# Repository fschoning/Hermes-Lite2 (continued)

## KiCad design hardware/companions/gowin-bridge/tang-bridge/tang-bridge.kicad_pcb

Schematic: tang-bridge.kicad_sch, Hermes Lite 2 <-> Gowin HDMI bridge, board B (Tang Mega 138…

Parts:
C1: 22pF; C_0402_1005Metric; LCSC C1555; not fitted
C2, C3, C4, C5, C6, C7, C8, C9, C10: 100nF; C_0402_1005Metric; LCSC C1525; not fitted
C11, C12, C13, C14, C15, C16, C17, C19, C21, C23: 100nF; C_0402_1005Metric; LCSC C1525
C18, C20, C22: 10uF; C_0805_2012Metric; LCSC C15850
D1, D2, D3, D4, D5, D6, D7, D8, D9: TPD4E05U06; USON-10_2.5x1.0mm_P0.5mm; LCSC C138714
H1, H2: M3; MountingHole_3.2mm_M3_Pad
J1: J14 2x20 socket; PinSocket_2x20_P2.54mm_Vertical; not fitted
J2: IN (HDMI); HDMI_A_Amphenol_10029449-x01xLF_Horizontal; LCSC C427307
J3: AUX (HDMI); HDMI_A_Amphenol_10029449-x01xLF_Horizontal; LCSC C427307
J4: OUT (HDMI); HDMI_A_Amphenol_10029449-x01xLF_Horizontal; LCSC C427307
J5: RX MODE; PinHeader_1x03_P2.54mm_Vertical; not fitted
J6: GND AUX; PinHeader_1x02_P2.54mm_Vertical; not fitted
J7: ROLE; PinHeader_1x03_P2.54mm_Vertical; not fitted
R1, R2, R3, R4, R17, R19, R21, R23, R25, R27, R29, R31: 22R; R_0402_1005Metric; LCSC C25092
R5, R6, R7, R8, R9, R10, R11, R12, R13, R14, R15, R16, R42: 0R; R_0402_1005Metric; LCSC C17168; not fitted
R18, R20, R22, R24, R26, R28, R30, R32, R34, R35, R41: 10k; R_0402_1005Metric; LCSC C25744
R33, R36, R37, R46, R47, R51, R52, R56, R57, R61, R62: 0R; R_0402_1005Metric; LCSC C17168
R38, R48, R53, R58, R63, R68, R69: 100R; R_0402_1005Metric; LCSC C25076
R39, R40: 100k; R_0402_1005Metric; LCSC C25741
R43, R44, R45: 0R; R_0805_2012Metric; LCSC C17477
R49, R50, R54, R55, R59, R60, R64, R65, R67: 4k7; R_0402_1005Metric; LCSC C25900; not fitted
R66: 10k; R_0402_1005Metric; LCSC C25744; not fitted
R70, R71: 100R; R_0402_1005Metric; LCSC C25076; not fitted
TP1: TP_LINK_CLK; TestPoint_Pad_D1.5mm
TP2: TP_LINK_D0; TestPoint_Pad_D1.5mm
TP3: TP_LINK_D1; TestPoint_Pad_D1.5mm
TP4: TP_LINK_D2; TestPoint_Pad_D1.5mm
TP5: TP_LINK_SLOW_IN; TestPoint_Pad_D1.5mm
TP6: TP_LINK_AUX_G1_CLK; TestPoint_Pad_D1.5mm
TP7: TP_LINK_AUX_G1_DAT; TestPoint_Pad_D1.5mm
TP8: TP_LINK_AUX_G2_CLK; TestPoint_Pad_D1.5mm
TP9: TP_LINK_AUX_G2_DAT; TestPoint_Pad_D1.5mm
TP10: TP_LINK_PRESENT; TestPoint_Pad_D1.5mm
TP11: TP_LINK_ROLE; TestPoint_Pad_D1.5mm
TP12: TP_LINK_REVCLK; TestPoint_Pad_D1.5mm
TP13: TP_LINK_R0; TestPoint_Pad_D1.5mm
TP14: TP_LINK_R1; TestPoint_Pad_D1.5mm
TP15: TP_LINK_R2; TestPoint_Pad_D1.5mm
TP16: TP_DRVI_REVCLK; TestPoint_Pad_D1.5mm
TP17: TP_ROLE; TestPoint_Pad_D1.5mm
TP18: TP_ROLE_N; TestPoint_Pad_D1.5mm
TP19: TP_RXO_AX_CLK; TestPoint_Pad_D1.5mm
TP20: TP_RXO_AX_D0; TestPoint_Pad_D1.5mm
TP21: TP_RXO_AX_D1; TestPoint_Pad_D1.5mm
TP22: TP_RXO_AX_D2; TestPoint_Pad_D1.5mm
TP23: TP_I_HPD; TestPoint_Pad_D1.5mm
TP24: TP_AX_HPD; TestPoint_Pad_D1.5mm
TP25: TP_O_HPD; TestPoint_Pad_D1.5mm
TP26: TP_AX_SLOW; TestPoint_Pad_D1.5mm
TP27: TP_O_SLOW; TestPoint_Pad_D1.5mm
TP28: TP_I_5V_PIN; TestPoint_Pad_D1.5mm
TP29: TP_AX_5V_PIN; TestPoint_Pad_D1.5mm
TP30: TP_O_5V_PIN; TestPoint_Pad_D1.5mm
TP31: TP_VBIAS; TestPoint_Pad_D1.5mm
TP32: TP_+3V3; TestPoint_Pad_D1.5mm
TP33: TP_P5V_J14; TestPoint_Pad_D1.5mm
TP34, TP35: TP_GND; TestPoint_THTPad_D2.0mm_Drill1.0mm
U1, U2: DS90LV048A; TSSOP-16_4.4x5mm_P0.65mm; LCSC C87137
U3, U4, U5: DS90LV047A; SOIC-16_3.9x9.9mm_P1.27mm; LCSC C206491
U6: SN74AVC4T245PW; TSSOP-16_4.4x5mm_P0.65mm; LCSC C81461
U7: AMS1117-3.3; SOT-223-3_TabPin2; LCSC C6186
U8: AO3400A; SOT-23; LCSC C20917

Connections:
+3V3: C11.1, C12.1, C13.1, C14.1, C15.1, C16.1, C17.1, C18.1, C19.1, C22.1, C23.1, J5.1, J7.1, R35.2, R41.2, R66.1, TP32.1, U1.13 (VCC), U1.16 (EN), U2.13 (VCC), U2.16 (EN), U3.1 (EN), U3.4 (VCC), U4.4 (VCC), U5.4 (VCC), U6.1 (VCCA), U6.2 (1DIR), U6.3 (2DIR), U6.16 (VCCB), U7.2 (VO)
AX_5V_PIN: D6.2 (D1-), J3.18 (+5V), TP29.1
AX_CLK_N: D4.1 (D1+), J3.12 (CK-), R16.1, R68.2, U2.1 (RIN1-), U4.16 (DOUT1-)
AX_CLK_P: D3.5 (D2-), J3.10 (CK+), R15.1, R68.1, U2.2 (RIN1+), U4.15 (DOUT1+)
AX_D0_N: D4.4 (D2+), J3.9 (D0-), R14.1, R69.2, U2.4 (RIN2-), U4.13 (DOUT2-)
AX_D0_P: D4.2 (D1-), J3.7 (D0+), R13.1, R69.1, U2.3 (RIN2+), U4.14 (DOUT2+)
AX_D1_N: D5.1 (D1+), J3.6 (D1-), R70.2, U2.5 (RIN3-), U5.16 (DOUT1-)
AX_D1_P: D4.5 (D2-), J3.4 (D1+), R70.1, U2.6 (RIN3+), U5.15 (DOUT1+)
AX_D2_N: D5.4 (D2+), J3.3 (D2-), R71.2, U2.8 (RIN4-), U5.13 (DOUT2-)
AX_D2_P: D5.2 (D1-), J3.1 (D2+), R71.1, U2.7 (RIN4+), U5.14 (DOUT2+)
AX_HPD: D6.1 (D1+), J3.19 (HPD/HEAC-), TP24.1
AX_SLOW: D5.5 (D2-), J3.15 (SCL), TP26.1
DRVI_AX_G1CLK: R25.2, R26.1, U4.2 (DIN1)
DRVI_AX_G1DAT: R27.2, R28.1, U4.3 (DIN2)
DRVI_AX_G2CLK: R29.2, R30.1, U5.2 (DIN1)
DRVI_AX_G2DAT: R31.2, R32.1, U5.3 (DIN2)
DRVI_R0: R19.2, R20.1, U3.3 (DIN2)
DRVI_R1: R21.2, R22.1, U3.6 (DIN3)
DRVI_R2: R23.2, R24.1, U3.7 (DIN4)
DRVI_REVCLK: R17.2, R18.1, TP16.1, U3.2 (DIN1)
GND: C1.2, C10.2, C11.2, C12.2, C13.2, C14.2, C15.2, C16.2, C17.2, C18.2, C19.2, C20.2, C21.2, C22.2, C23.2, D1.3 (GND), D1.8 (GND), D2.3 (GND), D2.8 (GND), D3.3 (GND), D3.8 (GND), D4.3 (GND), D4.8 (GND), D5.3 (GND), D5.8 (GND), D6.3 (GND), D6.8 (GND), D7.3 (GND), D7.8 (GND), D8.3 (GND), D8.8 (GND), D9.3 (GND), D9.8 (GND), H1.1, H2.1, J1.12, J2.2 (D2S), J2.5 (D1S), J2.8 (D0S), J2.11 (CKS), J2.17 (GND), J3.2 (D2S), J3.5 (D1S), J3.8 (D0S), J3.11 (CKS), J3.17 (GND), J4.2 (D2S), J4.5 (D1S), J4.8 (D0S), J4.11 (CKS), J4.17 (GND), J6.1, J6.2, J7.3, R18.2, R20.2, R22.2, R24.2, R26.2, R28.2, R30.2, R32.2, R34.2, R38.2, R39.2, R40.2, R43.2, R44.2, R45.2, R67.2, TP34.1, TP35.1, U1.12 (GND), U2.9 (~EN), U2.12 (GND), U3.5 (GND), U3.8 (~EN), U4.5 (GND), U4.6 (DIN3), U4.7 (DIN4), U4.8 (~EN), U5.5 (GND), U5.6 (DIN3), U5.7 (DIN4), U5.8 (~EN), U6.8 (GND), U6.9 (GND), U7.1 (GND), U8.2 (S)
I_5V_PIN: D3.4 (D2+), J2.18 (+5V), TP28.1
I_CLK_N: C3.1, D1.2 (D1-), J2.12 (CK-), R6.1, R47.1
I_CLK_P: C2.1, D1.1 (D1+), J2.10 (CK+), R5.1, R46.1
I_CLK_RX_N: C3.2, R47.2, R48.2, R50.2, U1.1 (RIN1-)
I_CLK_RX_P: C2.2, R46.2, R48.1, R49.2, U1.2 (RIN1+)
I_D0_N: C5.1, D1.5 (D2-), J2.9 (D0-), R8.1, R52.1
I_D0_P: C4.1, D1.4 (D2+), J2.7 (D0+), R7.1, R51.1
I_D0_RX_N: C5.2, R52.2, R53.2, R55.2, U1.4 (RIN2-)
I_D0_RX_P: C4.2, R51.2, R53.1, R54.2, U1.3 (RIN2+)
I_D1_N: C7.1, D2.2 (D1-), J2.6 (D1-), R10.1, R57.1
I_D1_P: C6.1, D2.1 (D1+), J2.4 (D1+), R9.1, R56.1
I_D1_RX_N: C7.2, R57.2, R58.2, R60.2, U1.5 (RIN3-)
I_D1_RX_P: C6.2, R56.2, R58.1, R59.2, U1.6 (RIN3+)
I_D2_N: C9.1, D2.5 (D2-), J2.3 (D2-), R12.1, R62.1
I_D2_P: C8.1, D2.4 (D2+), J2.1 (D2+), R11.1, R61.1
I_D2_RX_N: C9.2, R62.2, R63.2, R65.2, U1.8 (RIN4-)
I_D2_RX_P: C8.2, R61.2, R63.1, R64.2, U1.7 (RIN4+)
I_HPD: D3.2 (D1-), J2.19 (HPD/HEAC-), J5.3, R35.1, R36.1, TP23.1
I_SLOW: D3.1 (D1+), J2.15 (SCL), R33.1
LINK_AUX_G1_CLK: J1.32, R15.2, R25.1, TP6.1, U6.13 (1B1)
LINK_AUX_G1_DAT: J1.18, R13.2, R27.1, TP7.1, U6.12 (1B2)
LINK_AUX_G2_CLK: J1.17, R14.2, R29.1, TP8.1, U6.11 (2B1)
LINK_AUX_G2_DAT: J1.31, R16.2, R31.1, TP9.1, U6.10 (2B2)
LINK_CLK: J1.20, R1.2, R5.2, TP1.1
LINK_D0: J1.10, R2.2, R7.2, TP2.1
LINK_D1: J1.14, R3.2, R9.2, TP3.1
LINK_D2: J1.16, R4.2, R11.2, TP4.1
LINK_PRESENT: J1.33, R36.2, TP10.1
LINK_R0: J1.9, R8.2, R19.1, TP13.1
LINK_R1: J1.13, R10.2, R21.1, TP14.1
LINK_R2: J1.15, R12.2, R23.1, TP15.1
LINK_REVCLK: J1.35, R17.1, TP12.1
LINK_ROLE: J1.34, R37.2, TP11.1
LINK_RX_CLK: R1.1, U1.15 (ROUT1)
LINK_RX_D0: R2.1, U1.14 (ROUT2)
LINK_RX_D1: R3.1, U1.11 (ROUT3)
LINK_RX_D2: R4.1, U1.10 (ROUT4)
LINK_SLOW_IN: C1.1, J1.19, R6.2, R33.2, R34.1, TP5.1
O_5V_PIN: D9.1 (D1+), J4.18 (+5V), R42.2, TP30.1
O_CLK_N: D6.5 (D2-), J4.12 (CK-), U3.16 (DOUT1-)
O_CLK_P: D6.4 (D2+), J4.10 (CK+), U3.15 (DOUT1+)
O_D0_N: D7.2 (D1-), J4.9 (D0-), U3.13 (DOUT2-)
O_D0_P: D7.1 (D1+), J4.7 (D0+), U3.14 (DOUT2+)
O_D1_N: D7.5 (D2-), J4.6 (D1-), U3.12 (DOUT3-)
O_D1_P: D7.4 (D2+), J4.4 (D1+), U3.11 (DOUT3+)
O_D2_N: D8.2 (D1-), J4.3 (D2-), U3.9 (DOUT4-)
O_D2_P: D8.1 (D1+), J4.1 (D2+), U3.10 (DOUT4+)
O_HPD: D8.5 (D2-), J4.19 (HPD/HEAC-), R38.1, TP25.1
O_SLOW: D8.4 (D2+), J4.15 (SCL), TP27.1
P5V_J14: C20.1, C21.1, J1.11, R42.1, TP33.1, U7.3 (VI)
ROLE: J7.2, R37.1, R40.1, TP17.1, U4.1 (EN), U6.15 (1~OE), U8.1 (G)
ROLE_N: R41.1, TP18.1, U5.1 (EN), U6.14 (2~OE), U8.3 (D)
RXEN_N: J5.2, R39.1, U1.9 (~EN)
RXO_AX_CLK: TP19.1, U2.15 (ROUT1), U6.4 (1A1)
RXO_AX_D0: TP20.1, U2.14 (ROUT2), U6.5 (1A2)
RXO_AX_D1: TP21.1, U2.11 (ROUT3), U6.6 (2A1)
RXO_AX_D2: TP22.1, U2.10 (ROUT4), U6.7 (2A2)
SHLD1: J2.SH, R43.1
SHLD2: J3.SH, R44.1
SHLD3: J4.SH, R45.1
VBIAS: C10.1, R49.1, R50.1, R54.1, R55.1, R59.1, R60.1, R64.1, R65.1, R66.2, R67.1, TP31.1

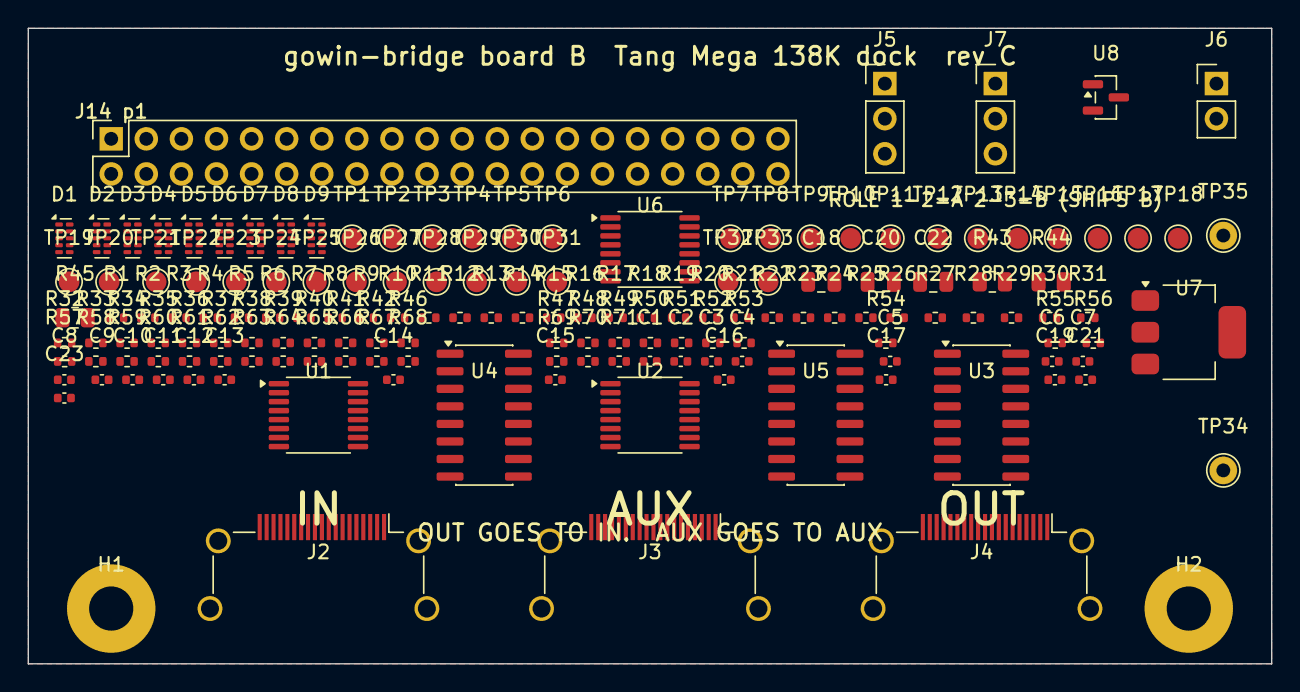
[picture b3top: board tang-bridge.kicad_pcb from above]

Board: 4 copper layers, 90.0 x 46.0 mm, 155 parts (1 on the bottom side), 82 nets, no tracks yet.

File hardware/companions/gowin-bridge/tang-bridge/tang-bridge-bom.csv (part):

Designator,Value,Footprint,LCSC,MfrPart,Populate,Function,Note
C1,22pF,C_0402_1005Metric,C1555,,DNP,Optional ringing damper on LINK_SLOW_IN,NOT FITTED. 22 pF into 100 R is 2.2 ns. Fit if the unterminated cable wire rings enough to double-clock the receiver.
C2,100nF,C_0402_1005Metric,C1525,,DNP,"AC-coupling option, I CLK P leg",NOT FITTED. Fit only together with the VBIAS network and remove the parallel 0 R link. Needs DC-balanced data; the gateware does not guarantee that.
C3,100nF,C_0402_1005Metric,C1525,,DNP,"AC-coupling option, I CLK N leg",NOT FITTED. Fit only together with the VBIAS network and remove the parallel 0 R link. Needs DC-balanced data; the gateware does not guarantee that.
C4,100nF,C_0402_1005Metric,C1525,,DNP,"AC-coupling option, I D0 P leg",NOT FITTED. Fit only together with the VBIAS network and remove the parallel 0 R link. Needs DC-balanced data; the gateware does not guarantee that.
C5,100nF,C_0402_1005Metric,C1525,,DNP,"AC-coupling option, I D0 N leg",NOT FITTED. Fit only together with the VBIAS network and remove the parallel 0 R link. Needs DC-balanced data; the gateware does not guarantee that.
C6,100nF,C_0402_1005Metric,C1525,,DNP,"AC-coupling option, I D1 P leg",NOT FITTED. Fit only together with the VBIAS network and remove the parallel 0 R link. Needs DC-balanced data; the gateware does not guarantee that.
C7,100nF,C_0402_1005Metric,C1525,,DNP,"AC-coupling option, I D1 N leg",NOT FITTED. Fit only together with the VBIAS network and remove the parallel 0 R link. Needs DC-balanced data; the gateware does not guarantee that.
C8,100nF,C_0402_1005Metric,C1525,,DNP,"AC-coupling option, I D2 P leg",NOT FITTED. Fit only together with the VBIAS network and remove the parallel 0 R link. Needs DC-balanced data; the gateware does not guarantee that.
C9,100nF,C_0402_1005Metric,C1525,,DNP,"AC-coupling option, I D2 N leg",NOT FITTED. Fit only together with the VBIAS network and remove the parallel 0 R link. Needs DC-balanced data; the gateware does not guarantee that.
C10,100nF,C_0402_1005Metric,C1525,,DNP,VBIAS bypass,NOT FITTED. Part of the AC-coupling option.
C11,100nF,C_0402_1005Metric,C1525,,yes,U1 VCC,
C12,100nF,C_0402_1005Metric,C1525,,yes,U2 VCC,
C13,100nF,C_0402_1005Metric,C1525,,yes,U3 VCC,
C14,100nF,C_0402_1005Metric,C1525,,yes,U4 VCC,
C15,100nF,C_0402_1005Metric,C1525,,yes,U5 VCC,
C16,100nF,C_0402_1005Metric,C1525,,yes,U6 VCCA,
C17,100nF,C_0402_1005Metric,C1525,,yes,U6 VCCB,
C18,10uF,C_0805_2012Metric,C15850,,yes,+3V3 bulk,
C19,100nF,C_0402_1005Metric,C1525,,yes,+3V3 bulk HF,
C20,10uF,C_0805_2012Metric,C15850,,yes,5 V input bulk,
C21,100nF,C_0402_1005Metric,C1525,,yes,5 V input HF,
C22,10uF,C_0805_2012Metric,C15850,,yes,U7 output bulk,
C23,100nF,C_0402_1005Metric,C1525,,yes,extra +3V3,
D1,TPD4E05U06,USON-10_2.5x1.0mm_P0.5mm,C138714,TPD4E05U06DQAR,yes,"Quad 0.5 pF ESD array, 5.5 V, USON-10","Place within 5 mm of the HDMI connector pins, on the connector side of everything else."
D2,TPD4E05U06,USON-10_2.5x1.0mm_P0.5mm,C138714,TPD4E05U06DQAR,yes,"Quad 0.5 pF ESD array, 5.5 V, USON-10","Place within 5 mm of the HDMI connector pins, on the connector side of everything else."
D3,TPD4E05U06,USON-10_2.5x1.0mm_P0.5mm,C138714,TPD4E05U06DQAR,yes,"Quad 0.5 pF ESD array, 5.5 V, USON-10","Place within 5 mm of the HDMI connector pins, on the connector side of everything else."
D4,TPD4E05U06,USON-10_2.5x1.0mm_P0.5mm,C138714,TPD4E05U06DQAR,yes,"Quad 0.5 pF ESD array, 5.5 V, USON-10","Place within 5 mm of the HDMI connector pins, on the connector side of everything else."
D5,TPD4E05U06,USON-10_2.5x1.0mm_P0.5mm,C138714,TPD4E05U06DQAR,yes,"Quad 0.5 pF ESD array, 5.5 V, USON-10","Place within 5 mm of the HDMI connector pins, on the connector side of everything else."
D6,TPD4E05U06,USON-10_2.5x1.0mm_P0.5mm,C138714,TPD4E05U06DQAR,yes,"Quad 0.5 pF ESD array, 5.5 V, USON-10","Place within 5 mm of the HDMI connector pins, on the connector side of everything else."
D7,TPD4E05U06,USON-10_2.5x1.0mm_P0.5mm,C138714,TPD4E05U06DQAR,yes,"Quad 0.5 pF ESD array, 5.5 V, USON-10","Place within 5 mm of the HDMI connector pins, on the connector side of everything else."
D8,TPD4E05U06,USON-10_2.5x1.0mm_P0.5mm,C138714,TPD4E05U06DQAR,yes,"Quad 0.5 pF ESD array, 5.5 V, USON-10","Place within 5 mm of the HDMI connector pins, on the connector side of everything else."
D9,TPD4E05U06,USON-10_2.5x1.0mm_P0.5mm,C138714,TPD4E05U06DQAR,yes,"Quad 0.5 pF ESD array, 5.5 V, USON-10","Place within 5 mm of the HDMI connector pins, on the connector side of everything else."
H1,M3,MountingHole_3.2mm_M3_Pad,,,yes,"M3 mounting hole, grounded",
H2,M3,MountingHole_3.2mm_M3_Pad,,,yes,"M3 mounting hole, grounded",
J1,J14 2x20 socket,PinSocket_2x20_P2.54mm_Vertical,,"2.54mm 2x20P vertical female header (e.g. BOOMELE, LCSC C5124634)",DNP,Mates the 2x20 male header the user solders into the Tang dock J14 holes (Bank 4). HAND SOLDERED,"HAND SOLDERED, not placed by JLCPCB: 40 through-hole pins, and as a distinct part number it would cost a $3.07 per-unique-Extended-part fee plus $1.31 of joint fees. You are already soldering the mating male header into the dock. Bottom side. J14 pin 36 (ball U17) is deliberately open: it is the one spare pin, and the gateware should leave it unconstrained. COST.md 5."
J2,IN (HDMI),HDMI_A_Amphenol_10029449-x01xLF_Horizontal,C427307,Amphenol ICC 10029449-111RLF,yes,"IN, cable 1: receives the 153.6 MHz link clock and lanes 0,1,2 at 307.2 Mbit/s, plus the HL2 status UART on SCL, which is the ONLY slow line with a destination in rev C","Hybrid mount: reflow the 19 SMT contacts, then solder the four through-hole shell legs. Mating face flush with the board edge."
J3,AUX (HDMI),HDMI_A_Amphenol_10029449-x01xLF_Horizontal,C427307,Amphenol ICC 10029449-111RLF,yes,"AUX, cable 3: bidirectional, full duplex. G1 = clock pair + data 0 pair, G2 = data 1 pair + data 2 pair. Board B ships strapped ROLE B, so it receives G1 and drives G2. SCL, HPD and +5 V are test pads only","Hybrid mount: reflow the 19 SMT contacts, then solder the four through-hole shell legs. Mating face flush with the board edge."
J4,OUT (HDMI),HDMI_A_Amphenol_10029449-x01xLF_Horizontal,C427307,Amphenol ICC 10029449-111RLF,yes,"OUT, cable 2: drives the reverse clock and reverse lanes 0,1,2 at 307.2 Mbit/s. Its SCL has no source in rev C (J14 pin 36 is left spare) and is a test pad only","Hybrid mount: reflow the 19 SMT contacts, then solder the four through-hole shell legs. Mating face flush with the board edge."
J5,RX MODE,PinHeader_1x03_P2.54mm_Vertical,,2.54mm 1x3P vertical pin header (e.g. LCSC C52016391),DNP,"IN receiver enable: 2-3 = auto, enabled only while a cable is in the IN socket (DEFAULT); 1-2 = force disabled, which is what the direct-LVDS experiment needs; no shunt = always enabled. Does NOT affect the AUX receiver",
J6,GND AUX,PinHeader_1x02_P2.54mm_Vertical,,2.54mm 1x2P vertical pin header (e.g. LCSC C52016390),DNP,Extra ground wire to a dock PMOD GND pin. J14 has only one ground pin and that is not enough for eight CMOS outputs switching at up to 307 Mbit/s - fit the wire,
J7,ROLE,PinHeader_1x03_P2.54mm_Vertical,,2.54mm 1x3P vertical pin header (e.g. LCSC C52016391),DNP,"ROLE strap, ONE shunt: 1-2 = ROLE A (drives AUX G1, receives G2); 2-3 = ROLE B (drives G2, receives G1) which is how board B ships. The two boards of a link must be strapped differently","Fit ONE shunt (LCSC C5305). Board B ships 2-3 = ROLE B, so the Gowin reads link_role LOW on J14 pin 34."
R1,22R,R_0402_1005Metric,C25092,,yes,"Receiver output damping into J14, LINK_CLK",
R2,22R,R_0402_1005Metric,C25092,,yes,"Receiver output damping into J14, LINK_D0",
R3,22R,R_0402_1005Metric,C25092,,yes,"Receiver output damping into J14, LINK_D1",
R4,22R,R_0402_1005Metric,C25092,,yes,"Receiver output damping into J14, LINK_D2",
R5,0R,R_0402_1005Metric,C17168,,DNP,Direct-LVDS link: I CLK + straight to the J14 A (T) leg,NOT FITTED. Fit only in direct-LVDS mode; see PINMAP.md 5.3.
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
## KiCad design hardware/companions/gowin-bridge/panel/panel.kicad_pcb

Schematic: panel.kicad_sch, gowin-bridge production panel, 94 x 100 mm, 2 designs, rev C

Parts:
C101, C102, C103, C104, C105, C106, C107, C108, C109, C202, C203, C204, C205, C206, C207, C208, C209, C210: 100nF; C_0402_1005Metric; LCSC C1525; not fitted
C110, C111, C112, C113, C114, C115, C116, C117, C118, C119, C120, C121, C122, C124, C126, C127, C211, C212, C213, C214, C215, C216, C217, C219, C221, C223: 100nF; C_0402_1005Metric; LCSC C1525
C123, C128, C129, C218, C220, C222: 10uF; C_0805_2012Metric; LCSC C15850
C125: 1uF; C_0402_1005Metric; LCSC C52923
C201: 22pF; C_0402_1005Metric; LCSC C1555; not fitted
D101, D102, D103, D104, D105, D106, D107, D108, D109, D201, D202, D203, D204, D205, D206, D207, D208, D209: TPD4E05U06; USON-10_2.5x1.0mm_P0.5mm; LCSC C138714
FID1, FID2, FID3: Fiducial; Fiducial_1mm_Mask2mm
H201, H202: M3; MountingHole_3.2mm_M3_Pad
J101: DB1 2x10 stack-through; PinSocket_2x10_P2.54mm_Vertical; not fitted
J102: DB12 2x03 socket; PinSocket_2x03_P2.54mm_Vertical; not fitted
J103: OUT (mini HDMI); HDMI_C_Mini_19P_Horizontal_Hybrid; LCSC C2682170
J104: AUX (mini HDMI); HDMI_C_Mini_19P_Horizontal_Hybrid; LCSC C2682170
J105: IN (mini HDMI); HDMI_C_Mini_19P_Horizontal_Hybrid; LCSC C2682170
J106: 3V3 SRC; PinHeader_1x03_P2.54mm_Vertical; not fitted
J107, J205: RX MODE; PinHeader_1x03_P2.54mm_Vertical; not fitted
J108: GND CLIP; PinHeader_1x02_P2.54mm_Vertical; not fitted
J109, J207: ROLE; PinHeader_1x03_P2.54mm_Vertical; not fitted
J201: J14 2x20 socket; PinSocket_2x20_P2.54mm_Vertical; not fitted
J202: IN (HDMI); HDMI_A_Amphenol_10029449-x01xLF_Horizontal; LCSC C427307
J203: AUX (HDMI); HDMI_A_Amphenol_10029449-x01xLF_Horizontal; LCSC C427307
J204: OUT (HDMI); HDMI_A_Amphenol_10029449-x01xLF_Horizontal; LCSC C427307
J206: GND AUX; PinHeader_1x02_P2.54mm_Vertical; not fitted
R101, R116, R117, R118, R119, R120, R121, R122, R123, R124, R136, R137, R141, R142, R146, R147, R151, R152, R233, R236, R237, R246, R247, R251, R252, R256, R257, R261, R262: 0R; R_0402_1005Metric; LCSC C17168
R102, R125, R126, R138, R143, R148, R153, R160, R161, R238, R248, R253, R258, R263, R268, R269: 100R; R_0402_1005Metric; LCSC C25076
R103, R104: 330R; R_0402_1005Metric; LCSC C25104
R105, R106, R107, R127, R130, R218, R220, R222, R224, R226, R228, R230, R232, R234, R235, R241: 10k; R_0402_1005Metric; LCSC C25744
R108, R109, R110, R111, R112, R113, R114, R115, R131, R132, R205, R206, R207, R208, R209, R210, R211, R212, R213, R214, R215, R216, R242: 0R; R_0402_1005Metric; LCSC C17168; not fitted
R128, R129, R239, R240: 100k; R_0402_1005Metric; LCSC C25741
R133, R134, R135, R243, R244, R245: 0R; R_0805_2012Metric; LCSC C17477
R139, R140, R144, R145, R149, R150, R154, R155, R157, R249, R250, R254, R255, R259, R260, R264, R265, R267: 4k7; R_0402_1005Metric; LCSC C25900; not fitted
R156, R266: 10k; R_0402_1005Metric; LCSC C25744; not fitted
R158, R159, R270, R271: 100R; R_0402_1005Metric; LCSC C25076; not fitted
R201, R202, R203, R204, R217, R219, R221, R223, R225, R227, R229, R231: 22R; R_0402_1005Metric; LCSC C25092
TP101: TP_HL2_CLK_RAW; TestPoint_Pad_D1.5mm
TP102: TP_HL2_CLK; TestPoint_Pad_D1.5mm
TP103: TP_HL2_O_D0; TestPoint_Pad_D1.5mm
TP104: TP_HL2_O_D1; TestPoint_Pad_D1.5mm
TP105: TP_HL2_O_D2; TestPoint_Pad_D1.5mm
TP106: TP_HL2_AX_G1CLK; TestPoint_Pad_D1.5mm
TP107: TP_HL2_AX_G1DAT; TestPoint_Pad_D1.5mm
TP108: TP_HL2_AX_G2CLK; TestPoint_Pad_D1.5mm
TP109: TP_HL2_AX_G2DAT; TestPoint_Pad_D1.5mm
TP110: TP_HL2_SLOW_OUT; TestPoint_Pad_D1.5mm
TP111: TP_HL2_I_D0; TestPoint_Pad_D1.5mm
TP112: TP_HL2_I_D1; TestPoint_Pad_D1.5mm
TP113: TP_HL2_I_D2; TestPoint_Pad_D1.5mm
TP114: TP_HL2_INCLK; TestPoint_Pad_D1.5mm
TP115: TP_HL2_ROLE_IN; TestPoint_Pad_D1.5mm
TP116, TP217: TP_ROLE; TestPoint_Pad_D1.5mm
TP117, TP218: TP_ROLE_N; TestPoint_Pad_D1.5mm
TP118: TP_DRVI_O_CLK; TestPoint_Pad_D1.5mm
TP119: TP_DRVI_AX_CLK; TestPoint_Pad_D1.5mm
TP120: TP_DRVI_AX_D1; TestPoint_Pad_D1.5mm
TP121: TP_RXO_I_CLK; TestPoint_Pad_D1.5mm
TP122: TP_RXO_I_D0; TestPoint_Pad_D1.5mm
TP123: TP_RXO_I_D1; TestPoint_Pad_D1.5mm
TP124: TP_RXO_I_D2; TestPoint_Pad_D1.5mm
TP125, TP219: TP_RXO_AX_CLK; TestPoint_Pad_D1.5mm
TP126, TP220: TP_RXO_AX_D0; TestPoint_Pad_D1.5mm
TP127, TP221: TP_RXO_AX_D1; TestPoint_Pad_D1.5mm
TP128, TP222: TP_RXO_AX_D2; TestPoint_Pad_D1.5mm
TP129: TP_X_SP1; TestPoint_Pad_D1.5mm
TP130: TP_X_SP2; TestPoint_Pad_D1.5mm
TP131, TP225: TP_O_HPD; TestPoint_Pad_D1.5mm
TP132, TP224: TP_AX_HPD; TestPoint_Pad_D1.5mm
TP133, TP223: TP_I_HPD; TestPoint_Pad_D1.5mm
TP134, TP226: TP_AX_SLOW; TestPoint_Pad_D1.5mm
TP135: TP_I_SLOW; TestPoint_Pad_D1.5mm
TP136, TP230: TP_O_5V_PIN; TestPoint_Pad_D1.5mm
TP137, TP229: TP_AX_5V_PIN; TestPoint_Pad_D1.5mm
TP138, TP228: TP_I_5V_PIN; TestPoint_Pad_D1.5mm
TP139, TP231: TP_VBIAS; TestPoint_Pad_D1.5mm
TP140: TP_SCL1; TestPoint_Pad_D1.5mm
TP141: TP_SDA1; TestPoint_Pad_D1.5mm
TP142: TP_VLVDS; TestPoint_Pad_D1.5mm
TP143, TP232: TP_+3V3; TestPoint_Pad_D1.5mm
TP144: TP_+2V5; TestPoint_Pad_D1.5mm
TP145: TP_DB1_3V3; TestPoint_Pad_D1.5mm
TP146, TP147, TP234, TP235: TP_GND; TestPoint_THTPad_D2.0mm_Drill1.0mm
TP201: TP_LINK_CLK; TestPoint_Pad_D1.5mm
TP202: TP_LINK_D0; TestPoint_Pad_D1.5mm
TP203: TP_LINK_D1; TestPoint_Pad_D1.5mm
TP204: TP_LINK_D2; TestPoint_Pad_D1.5mm
TP205: TP_LINK_SLOW_IN; TestPoint_Pad_D1.5mm
TP206: TP_LINK_AUX_G1_CLK; TestPoint_Pad_D1.5mm
TP207: TP_LINK_AUX_G1_DAT; TestPoint_Pad_D1.5mm
TP208: TP_LINK_AUX_G2_CLK; TestPoint_Pad_D1.5mm
TP209: TP_LINK_AUX_G2_DAT; TestPoint_Pad_D1.5mm
TP210: TP_LINK_PRESENT; TestPoint_Pad_D1.5mm
TP211: TP_LINK_ROLE; TestPoint_Pad_D1.5mm
TP212: TP_LINK_REVCLK; TestPoint_Pad_D1.5mm
TP213: TP_LINK_R0; TestPoint_Pad_D1.5mm
TP214: TP_LINK_R1; TestPoint_Pad_D1.5mm
TP215: TP_LINK_R2; TestPoint_Pad_D1.5mm
TP216: TP_DRVI_REVCLK; TestPoint_Pad_D1.5mm
TP227: TP_O_SLOW; TestPoint_Pad_D1.5mm
TP233: TP_P5V_J14; TestPoint_Pad_D1.5mm
U101, U107, U108, U112, U206: SN74AVC4T245PW; TSSOP-16_4.4x5mm_P0.65mm; LCSC C81461
U102, U103, U104, U203, U204, U205: DS90LV047A; SOIC-16_3.9x9.9mm_P1.27mm; LCSC C206491
U105, U106, U201, U202: DS90LV048A; TSSOP-16_4.4x5mm_P0.65mm; LCSC C87137
U109: ME6211C25M5G; SOT-23-5; LCSC C194395
U110: AMS1117-3.3; SOT-223-3_TabPin2; LCSC C6186; not fitted
U111, U208: AO3400A; SOT-23; LCSC C20917
U207: AMS1117-3.3; SOT-223-3_TabPin2; LCSC C6186

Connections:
A_+2V5: C111.1, C113.1, C120.1, C122.1, C125.1, R132.2, TP144.1, U101.1 (VCCA), U101.2 (1DIR), U101.3 (2DIR), U107.16 (VCCB), U108.16 (VCCB), U109.5 (V_{OUT}), U112.1 (VCCA), U112.2 (1DIR), U112.3 (2DIR)
A_+3V3: C110.1, C112.1, C114.1, C115.1, C116.1, C117.1, C118.1, C119.1, C121.1, C123.1, C124.1, C126.1, J106.2, J107.1, J109.1, R127.2, R130.2, R156.1, TP143.1, U101.16 (VCCB), U102.1 (EN), U102.4 (VCC), U103.4 (VCC), U104.4 (VCC), U105.13 (VCC), U105.16 (EN), U106.13 (VCC), U106.16 (EN), U107.1 (VCCA), U107.2 (1DIR), U107.3 (2DIR), U108.1 (VCCA), U108.2 (1DIR), U108.3 (2DIR), U108.14 (2~OE), U109.1 (V_{IN}), U109.3 (CE), U112.16 (VCCB)
A_AX_5V_PIN: D106.2 (D1-), J104.18 (+5V), TP137.1
A_AX_CLK_N: D104.1 (D1+), J104.12 (CK-), R158.2, U103.16 (DOUT1-), U106.1 (RIN1-)
A_AX_CLK_P: D103.5 (D2-), J104.11 (CK+), R158.1, U103.15 (DOUT1+), U106.2 (RIN1+)
A_AX_D0_N: D104.4 (D2+), J104.9 (D0-), R159.2, U103.13 (DOUT2-), U106.4 (RIN2-)
A_AX_D0_P: D104.2 (D1-), J104.8 (D0+), R159.1, U103.14 (DOUT2+), U106.3 (RIN2+)
A_AX_D1_N: D105.1 (D1+), J104.6 (D1-), R160.2, U104.16 (DOUT1-), U106.5 (RIN3-)
A_AX_D1_P: D104.5 (D2-), J104.5 (D1+), R160.1, U104.15 (DOUT1+), U106.6 (RIN3+)
A_AX_D2_N: D105.4 (D2+), J104.3 (D2-), R161.2, U104.13 (DOUT2-), U106.8 (RIN4-)
A_AX_D2_P: D105.2 (D1-), J104.2 (D2+), R161.1, U104.14 (DOUT2+), U106.7 (RIN4+)
A_AX_HPD: D106.1 (D1+), J104.19 (HPD/HEAC-), TP132.1
A_AX_SLOW: D105.5 (D2-), J104.15 (SCL), TP134.1
A_DB1_3V3: C127.1, J101.19, J101.20, J106.1, TP145.1
A_DRVI_AX_CLK: R112.2, TP119.1, U103.2 (DIN1), U112.13 (1B1)
A_DRVI_AX_D0: R113.2, U103.3 (DIN2), U112.12 (1B2)
A_DRVI_AX_D1: R114.2, TP120.1, U104.2 (DIN1), U112.11 (2B1)
A_DRVI_AX_D2: R115.2, U104.3 (DIN2), U112.10 (2B2)
A_DRVI_O_CLK: R108.2, TP118.1, U101.13 (1B1), U102.2 (DIN1)
A_DRVI_O_D0: R109.2, U101.12 (1B2), U102.3 (DIN2)
A_DRVI_O_D1: R110.2, U101.11 (2B1), U102.6 (DIN3)
A_DRVI_O_D2: R111.2, U101.10 (2B2), U102.7 (DIN4)
A_HL2_AX_G1DAT: J102.2, R105.1, R113.1, R122.2, TP107.1, U112.5 (1A2)
A_HL2_AX_G2DAT: J101.4, R107.1, R115.1, R124.2, TP109.1, U112.7 (2A2)
A_HL2_INCLK: J102.6, R119.2, TP114.1
A_HL2_I_D0: J101.11, R116.2, TP111.1
A_HL2_I_D1: J101.15, R117.2, TP112.1
A_HL2_I_D2: J101.17, R118.2, TP113.1
A_HL2_ROLE_IN: J102.5, R120.2, TP115.1
A_HL2_SLOW_OUT: J102.1, R125.1, TP110.1
A_I_5V_PIN: D109.1 (D1+), J105.18 (+5V), R131.1, TP138.1
A_I_CLK_N: C102.1, D106.5 (D2-), J105.12 (CK-), R137.1
A_I_CLK_P: C101.1, D106.4 (D2+), J105.11 (CK+), R136.1
A_I_CLK_RX_N: C102.2, R137.2, R138.2, R140.2, U105.1 (RIN1-)
A_I_CLK_RX_P: C101.2, R136.2, R138.1, R139.2, U105.2 (RIN1+)
A_I_D0_N: C104.1, D107.2 (D1-), J105.9 (D0-), R142.1
A_I_D0_P: C103.1, D107.1 (D1+), J105.8 (D0+), R141.1
A_I_D0_RX_N: C104.2, R142.2, R143.2, R145.2, U105.4 (RIN2-)
A_I_D0_RX_P: C103.2, R141.2, R143.1, R144.2, U105.3 (RIN2+)
A_I_D1_N: C106.1, D107.5 (D2-), J105.6 (D1-), R147.1
A_I_D1_P: C105.1, D107.4 (D2+), J105.5 (D1+), R146.1
A_I_D1_RX_N: C106.2, R147.2, R148.2, R150.2, U105.5 (RIN3-)
A_I_D1_RX_P: C105.2, R146.2, R148.1, R149.2, U105.6 (RIN3+)
A_I_D2_N: C108.1, D108.2 (D1-), J105.3 (D2-), R152.1
A_I_D2_P: C107.1, D108.1 (D1+), J105.2 (D2+), R151.1
A_I_D2_RX_N: C108.2, R152.2, R153.2, R155.2, U105.8 (RIN4-)
A_I_D2_RX_P: C107.2, R151.2, R153.1, R154.2, U105.7 (RIN4+)
A_I_HPD: D108.5 (D2-), J105.19 (HPD/HEAC-), J107.3, R127.1, TP133.1
A_I_SLOW: D108.4 (D2+), J105.15 (SCL), TP135.1
A_LDO3V3: C129.1, J106.3, U110.2 (VO)
A_O_5V_PIN: D103.4 (D2+), J103.18 (+5V), TP136.1
A_O_CLK_N: D101.2 (D1-), J103.12 (CK-), U102.16 (DOUT1-)
A_O_CLK_P: D101.1 (D1+), J103.11 (CK+), U102.15 (DOUT1+)
A_O_D0_N: D101.5 (D2-), J103.9 (D0-), U102.13 (DOUT2-)
A_O_D0_P: D101.4 (D2+), J103.8 (D0+), U102.14 (DOUT2+)
A_O_D1_N: D102.2 (D1-), J103.6 (D1-), U102.12 (DOUT3-)
A_O_D1_P: D102.1 (D1+), J103.5 (D1+), U102.11 (DOUT3+)
A_O_D2_N: D102.5 (D2-), J103.3 (D2-), U102.9 (DOUT4-)
A_O_D2_P: D102.4 (D2+), J103.2 (D2+), U102.10 (DOUT4+)
A_O_HPD: D103.2 (D1-), J103.19 (HPD/HEAC-), R126.1, TP131.1
A_O_SLOW: D103.1 (D1+), J103.15 (SCL), R125.2
A_P5V_IN: C128.1, R131.2, U110.3 (VI)
A_ROLE: J109.2, R129.1, TP116.1, U103.1 (EN), U107.5 (1A2), U108.15 (1~OE), U111.1 (G)
A_ROLE_N: R130.1, TP117.1, U104.1 (EN), U107.14 (2~OE), U111.3 (D)
A_RXEN_N: J107.2, R128.1, U105.9 (~EN)
A_RXO_AX_CLK: TP125.1, U106.15 (ROUT1), U108.4 (1A1)
A_RXO_AX_D0: TP126.1, U106.14 (ROUT2), U108.5 (1A2)
A_RXO_AX_D1: TP127.1, U106.11 (ROUT3), U107.6 (2A1)
A_RXO_AX_D2: TP128.1, U106.10 (ROUT4), U107.7 (2A2)
A_RXO_I_CLK: TP121.1, U105.15 (ROUT1), U107.4 (1A1)
A_RXO_I_D0: R116.1, TP122.1, U105.14 (ROUT2)
A_RXO_I_D1: R117.1, TP123.1, U105.11 (ROUT3)
A_RXO_I_D2: R118.1, TP124.1, U105.10 (ROUT4)
A_SCL1: J101.16, TP140.1
A_SDA1: J101.18, TP141.1
A_SHLD1: J103.SH, R133.1
A_SHLD2: J104.SH, R134.1
A_SHLD3: J105.SH, R135.1
A_VBIAS: C109.1, R139.1, R140.1, R144.1, R145.1, R149.1, R150.1, R154.1, R155.1, R156.2, R157.1, TP139.1
A_VLVDS: J101.7, J101.8, R132.1, TP142.1
A_X_AXG1CLK25: R121.1, U108.13 (1B1)
A_X_AXG1DAT25: R122.1, U108.12 (1B2)
A_X_AXG2CLK25: R123.1, U107.11 (2B1)
A_X_AXG2DAT25: R124.1, U107.10 (2B2)
A_X_INCLK25: R119.1, U107.13 (1B1)
A_X_ROLE25: R120.1, U107.12 (1B2)
A_X_SP1: TP129.1, U108.11 (2B1)
A_X_SP2: TP130.1, U108.10 (2B2)
B_+3V3: C211.1, C212.1, C213.1, C214.1, C215.1, C216.1, C217.1, C218.1, C219.1, C222.1, C223.1, J205.1, J207.1, R235.2, R241.2, R266.1, TP232.1, U201.13 (VCC), U201.16 (EN), U202.13 (VCC), U202.16 (EN), U203.1 (EN), U203.4 (VCC), U204.4 (VCC), U205.4 (VCC), U206.1 (VCCA), U206.2 (1DIR), U206.3 (2DIR), U206.16 (VCCB), U207.2 (VO)
B_AX_5V_PIN: D206.2 (D1-), J203.18 (+5V), TP229.1
B_AX_CLK_N: D204.1 (D1+), J203.12 (CK-), R216.1, R268.2, U202.1 (RIN1-), U204.16 (DOUT1-)
B_AX_CLK_P: D203.5 (D2-), J203.10 (CK+), R215.1, R268.1, U202.2 (RIN1+), U204.15 (DOUT1+)
B_AX_D0_N: D204.4 (D2+), J203.9 (D0-), R214.1, R269.2, U202.4 (RIN2-), U204.13 (DOUT2-)
B_AX_D0_P: D204.2 (D1-), J203.7 (D0+), R213.1, R269.1, U202.3 (RIN2+), U204.14 (DOUT2+)
B_AX_D1_N: D205.1 (D1+), J203.6 (D1-), R270.2, U202.5 (RIN3-), U205.16 (DOUT1-)
B_AX_D1_P: D204.5 (D2-), J203.4 (D1+), R270.1, U202.6 (RIN3+), U205.15 (DOUT1+)
B_AX_D2_N: D205.4 (D2+), J203.3 (D2-), R271.2, U202.8 (RIN4-), U205.13 (DOUT2-)
B_AX_D2_P: D205.2 (D1-), J203.1 (D2+), R271.1, U202.7 (RIN4+), U205.14 (DOUT2+)
B_AX_HPD: D206.1 (D1+), J203.19 (HPD/HEAC-), TP224.1
B_AX_SLOW: D205.5 (D2-), J203.15 (SCL), TP226.1
B_DRVI_AX_G1CLK: R225.2, R226.1, U204.2 (DIN1)
B_DRVI_AX_G1DAT: R227.2, R228.1, U204.3 (DIN2)
B_DRVI_AX_G2CLK: R229.2, R230.1, U205.2 (DIN1)
B_DRVI_AX_G2DAT: R231.2, R232.1, U205.3 (DIN2)
B_DRVI_R0: R219.2, R220.1, U203.3 (DIN2)
B_DRVI_R1: R221.2, R222.1, U203.6 (DIN3)
B_DRVI_R2: R223.2, R224.1, U203.7 (DIN4)
B_DRVI_REVCLK: R217.2, R218.1, TP216.1, U203.2 (DIN1)
B_GND: C201.2, C210.2, C211.2, C212.2, C213.2, C214.2, C215.2, C216.2, C217.2, C218.2, C219.2, C220.2, C221.2, C222.2, C223.2, D201.3 (GND), D201.8 (GND), D202.3 (GND), D202.8 (GND), D203.3 (GND), D203.8 (GND), D204.3 (GND), D204.8 (GND), D205.3 (GND), D205.8 (GND), D206.3 (GND), D206.8 (GND), D207.3 (GND), D207.8 (GND), D208.3 (GND), D208.8 (GND), D209.3 (GND), D209.8 (GND), H201.1, H202.1, J201.12, J202.2 (D2S), J202.5 (D1S), J202.8 (D0S), J202.11 (CKS), J202.17 (GND), J203.2 (D2S), J203.5 (D1S), J203.8 (D0S), J203.11 (CKS), J203.17 (GND), J204.2 (D2S), J204.5 (D1S), J204.8 (D0S), J204.11 (CKS), J204.17 (GND), J206.1, J206.2, J207.3, R218.2, R220.2, R222.2, R224.2, R226.2, R228.2, R230.2, R232.2, R234.2, R238.2, R239.2, R240.2, R243.2, R244.2, R245.2, R267.2, TP234.1, TP235.1, U201.12 (GND), U202.9 (~EN), U202.12 (GND), U203.5 (GND), U203.8 (~EN), U204.5 (GND), U204.6 (DIN3), U204.7 (DIN4), U204.8 (~EN), U205.5 (GND), U205.6 (DIN3), U205.7 (DIN4), U205.8 (~EN), U206.8 (GND), U206.9 (GND), U207.1 (GND), U208.2 (S)
B_I_5V_PIN: D203.4 (D2+), J202.18 (+5V), TP228.1
B_I_CLK_N: C203.1, D201.2 (D1-), J202.12 (CK-), R206.1, R247.1
B_I_CLK_P: C202.1, D201.1 (D1+), J202.10 (CK+), R205.1, R246.1
B_I_CLK_RX_N: C203.2, R247.2, R248.2, R250.2, U201.1 (RIN1-)
B_I_CLK_RX_P: C202.2, R246.2, R248.1, R249.2, U201.2 (RIN1+)
B_I_D0_N: C205.1, D201.5 (D2-), J202.9 (D0-), R208.1, R252.1
B_I_D0_P: C204.1, D201.4 (D2+), J202.7 (D0+), R207.1, R251.1
B_I_D0_RX_N: C205.2, R252.2, R253.2, R255.2, U201.4 (RIN2-)
B_I_D0_RX_P: C204.2, R251.2, R253.1, R254.2, U201.3 (RIN2+)
B_I_D1_N: C207.1, D202.2 (D1-), J202.6 (D1-), R210.1, R257.1
B_I_D1_P: C206.1, D202.1 (D1+), J202.4 (D1+), R209.1, R256.1
B_I_D1_RX_N: C207.2, R257.2, R258.2, R260.2, U201.5 (RIN3-)
B_I_D1_RX_P: C206.2, R256.2, R258.1, R259.2, U201.6 (RIN3+)
B_I_D2_N: C209.1, D202.5 (D2-), J202.3 (D2-), R212.1, R262.1
B_I_D2_P: C208.1, D202.4 (D2+), J202.1 (D2+), R211.1, R261.1
B_I_D2_RX_N: C209.2, R262.2, R263.2, R265.2, U201.8 (RIN4-)
B_I_D2_RX_P: C208.2, R261.2, R263.1, R264.2, U201.7 (RIN4+)
B_I_HPD: D203.2 (D1-), J202.19 (HPD/HEAC-), J205.3, R235.1, R236.1, TP223.1
B_I_SLOW: D203.1 (D1+), J202.15 (SCL), R233.1
B_LINK_AUX_G1_CLK: J201.32, R215.2, R225.1, TP206.1, U206.13 (1B1)
B_LINK_AUX_G1_DAT: J201.18, R213.2, R227.1, TP207.1, U206.12 (1B2)
B_LINK_AUX_G2_CLK: J201.17, R214.2, R229.1, TP208.1, U206.11 (2B1)
B_LINK_AUX_G2_DAT: J201.31, R216.2, R231.1, TP209.1, U206.10 (2B2)
B_LINK_CLK: J201.20, R201.2, R205.2, TP201.1
B_LINK_D0: J201.10, R202.2, R207.2, TP202.1
B_LINK_D1: J201.14, R203.2, R209.2, TP203.1
B_LINK_D2: J201.16, R204.2, R211.2, TP204.1
B_LINK_PRESENT: J201.33, R236.2, TP210.1
B_LINK_R0: J201.9, R208.2, R219.1, TP213.1
B_LINK_R1: J201.13, R210.2, R221.1, TP214.1
B_LINK_R2: J201.15, R212.2, R223.1, TP215.1
B_LINK_REVCLK: J201.35, R217.1, TP212.1
B_LINK_ROLE: J201.34, R237.2, TP211.1
B_LINK_RX_CLK: R201.1, U201.15 (ROUT1)
B_LINK_RX_D0: R202.1, U201.14 (ROUT2)
B_LINK_RX_D1: R203.1, U201.11 (ROUT3)
B_LINK_RX_D2: R204.1, U201.10 (ROUT4)
B_LINK_SLOW_IN: C201.1, J201.19, R206.2, R233.2, R234.1, TP205.1
B_O_5V_PIN: D209.1 (D1+), J204.18 (+5V), R242.2, TP230.1
B_O_CLK_N: D206.5 (D2-), J204.12 (CK-), U203.16 (DOUT1-)
B_O_CLK_P: D206.4 (D2+), J204.10 (CK+), U203.15 (DOUT1+)
B_O_D0_N: D207.2 (D1-), J204.9 (D0-), U203.13 (DOUT2-)
B_O_D0_P: D207.1 (D1+), J204.7 (D0+), U203.14 (DOUT2+)
B_O_D1_N: D207.5 (D2-), J204.6 (D1-), U203.12 (DOUT3-)
B_O_D1_P: D207.4 (D2+), J204.4 (D1+), U203.11 (DOUT3+)
B_O_D2_N: D208.2 (D1-), J204.3 (D2-), U203.9 (DOUT4-)
B_O_D2_P: D208.1 (D1+), J204.1 (D2+), U203.10 (DOUT4+)
B_O_HPD: D208.5 (D2-), J204.19 (HPD/HEAC-), R238.1, TP225.1
B_O_SLOW: D208.4 (D2+), J204.15 (SCL), TP227.1
B_P5V_J14: C220.1, C221.1, J201.11, R242.1, TP233.1, U207.3 (VI)
B_ROLE: J207.2, R237.1, R240.1, TP217.1, U204.1 (EN), U206.15 (1~OE), U208.1 (G)
B_ROLE_N: R241.1, TP218.1, U205.1 (EN), U206.14 (2~OE), U208.3 (D)
B_RXEN_N: J205.2, R239.1, U201.9 (~EN)
B_RXO_AX_CLK: TP219.1, U202.15 (ROUT1), U206.4 (1A1)
B_RXO_AX_D0: TP220.1, U202.14 (ROUT2), U206.5 (1A2)
B_RXO_AX_D1: TP221.1, U202.11 (ROUT3), U206.6 (2A1)
B_RXO_AX_D2: TP222.1, U202.10 (ROUT4), U206.7 (2A2)
B_SHLD1: J202.SH, R243.1
B_SHLD2: J203.SH, R244.1
B_SHLD3: J204.SH, R245.1
B_VBIAS: C210.1, R249.1, R250.1, R254.1, R255.1, R259.1, R260.1, R264.1, R265.1, R266.2, R267.1, TP231.1

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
